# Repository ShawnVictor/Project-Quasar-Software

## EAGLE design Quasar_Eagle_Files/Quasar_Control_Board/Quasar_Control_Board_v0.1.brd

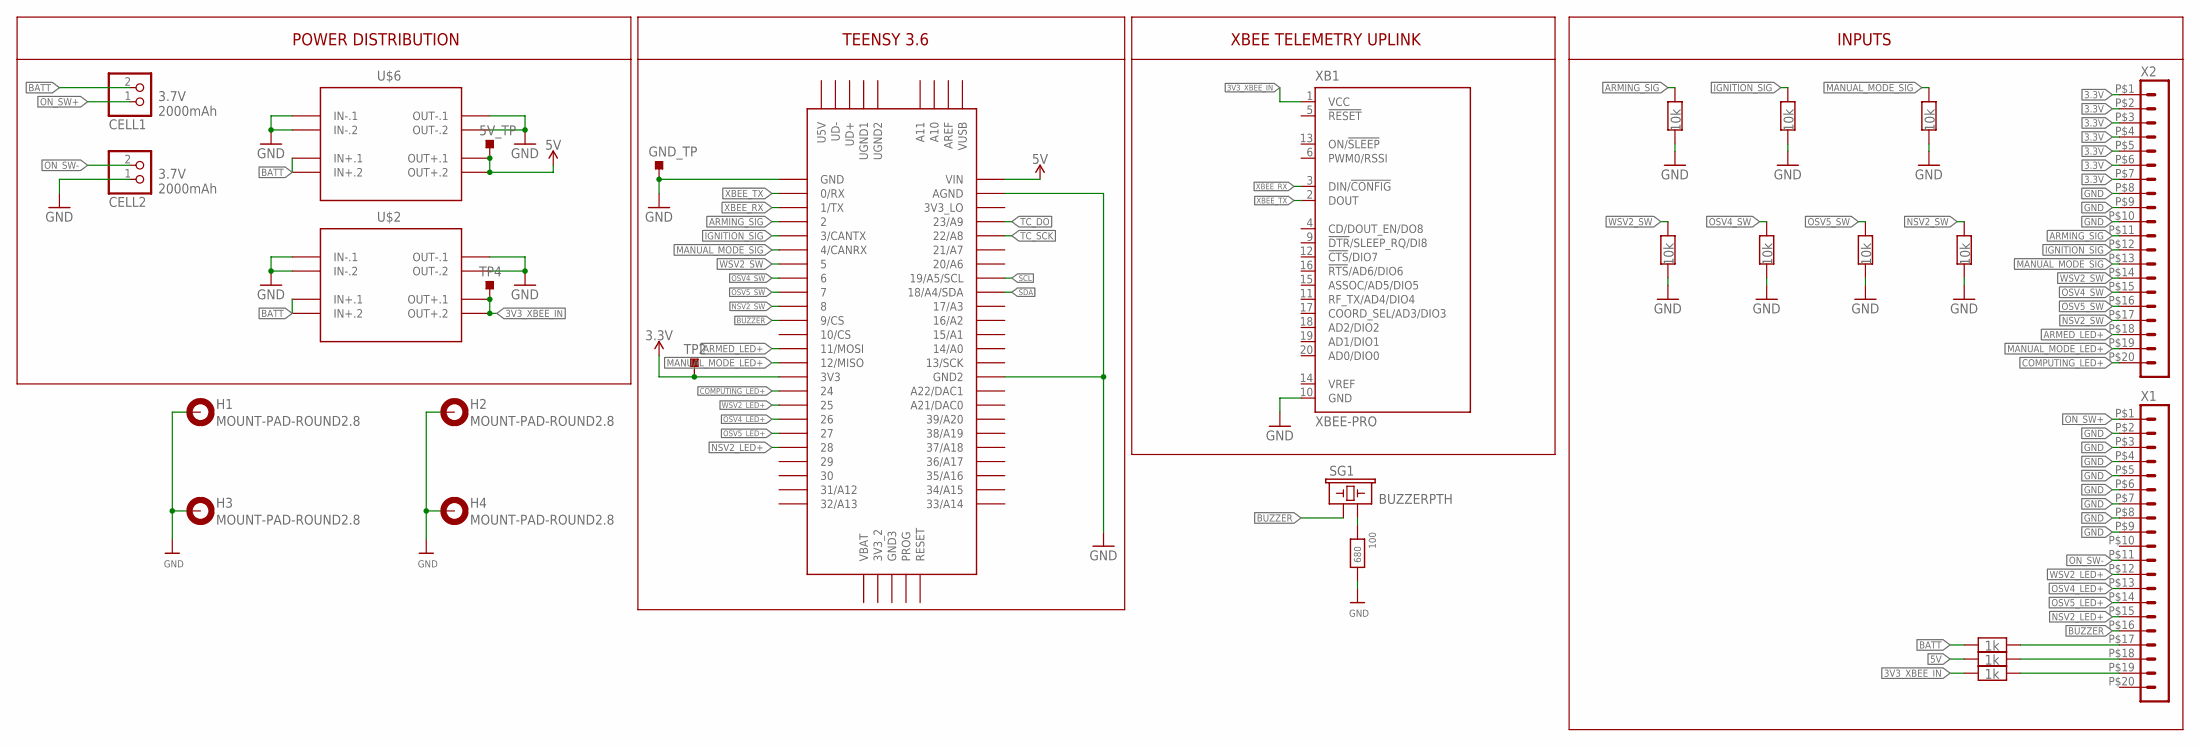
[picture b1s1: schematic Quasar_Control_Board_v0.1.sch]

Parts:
5V_TP: TESTPOINT_TPS-SMD-10SN; TESTPOINT_SMD-10SN
100: 680; 0603
CELL1, CELL2: JSTPH; JSTPH2
GND_TP: TESTPOINT_TPS-SMD-10SN; TESTPOINT_SMD-10SN
H1, H2, H3, H4: MOUNT-PAD-ROUND2.8; 2,8-PAD
R1, R2, R3, R4, R5, R6, R7: 10k; 0805
R8, R9, R10: 1k; 0805
SG1: BUZZERPTH; BUZZER-12MM
TP2, TP4: TESTPOINT_TPS-SMD-10SN; TESTPOINT_SMD-10SN
U$1: TEENSY_3.5/3.6
U$2, U$6: 12V_LC_REG; DC-DC-STEP-DOWN-MP1584
X1, X2: HEADER_POS20_44914-2001; 44914-2001
XB1: XBEE-PRO

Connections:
3.3V: TP2.TP, U$1.3V3, X2.P$1 (1), X2.P$2 (2), X2.P$3 (3), X2.P$4 (4), X2.P$5 (5), X2.P$6 (6), X2.P$7 (7)
3V3_XBEE_IN: R10.2, TP4.TP, U$2.OUT+.1, U$2.OUT+.2, XB1.1 (VCC)
5V: 5V_TP.TP, R9.2, U$1.VIN, U$6.OUT+.1, U$6.OUT+.2
ARMED_LED+: U$1.11/MOSI, X2.P$18 (18)
ARMING_SIG: R1.1, U$1.2, X2.P$11 (11)
BATT: CELL1.2, R8.2, U$2.IN+.1, U$2.IN+.2, U$6.IN+.1, U$6.IN+.2
BUZZER: SG1.+ (1), U$1.9/CS, X1.P$16 (16)
COMPUTING_LED+: U$1.24, X2.P$20 (20)
GND: 100.2, CELL2.1, GND_TP.TP, H1.B2,8, H2.B2,8, H3.B2,8, H4.B2,8, R1.2, R2.2, R3.2, R4.2, R5.2, R6.2, R7.2, U$1.AGND, U$1.GND, U$1.GND2, U$2.IN-.1, U$2.IN-.2, U$2.OUT-.1, U$2.OUT-.2, U$6.IN-.1, U$6.IN-.2, U$6.OUT-.1, U$6.OUT-.2, X1.P$2 (2), X1.P$3 (3), X1.P$4 (4), X1.P$5 (5), X1.P$6 (6), X1.P$7 (7), X1.P$8 (8), X1.P$9 (9), X2.P$8 (8), X2.P$9 (9), X2.P$10 (10), XB1.10 (GND)
IGNITION_SIG: R2.1, U$1.3/CANTX, X2.P$12 (12)
MANUAL_MODE_LED+: U$1.12/MISO, X2.P$19 (19)
MANUAL_MODE_SIG: R3.1, U$1.4/CANRX, X2.P$13 (13)
unnamed: R8.1, X1.P$17 (17)
unnamed: R9.1, X1.P$18 (18)
unnamed: R10.1, X1.P$19 (19)
unnamed: 100.1, SG1.- (2)
NSV2_LED+: U$1.28, X1.P$15 (15)
NSV2_SW: R7.1, U$1.8, X2.P$17 (17)
ON_SW+: CELL1.1, X1.P$1 (1)
ON_SW-: CELL2.2, X1.P$11 (11)
OSV4_LED+: U$1.26, X1.P$13 (13)
OSV4_SW: R5.1, U$1.6, X2.P$15 (15)
OSV5_LED+: U$1.27, X1.P$14 (14)
OSV5_SW: R6.1, U$1.7, X2.P$16 (16)
SCL: U$1.19/A5/SCL
SDA: U$1.18/A4/SDA
TC_DO: U$1.23/A9
TC_SCK: U$1.22/A8
WSV2_LED+: U$1.25, X1.P$12 (12)
WSV2_SW: R4.1, U$1.5, X2.P$14 (14)
XBEE_RX: U$1.1/TX, XB1.3 (DIN/!CONFIG)
XBEE_TX: U$1.0/RX, XB1.2 (DOUT)

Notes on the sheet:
TEENSY 3.6
XBEE TELEMETRY UPLINK
POWER DISTRIBUTION
3.7V 2000mAh
INPUTS

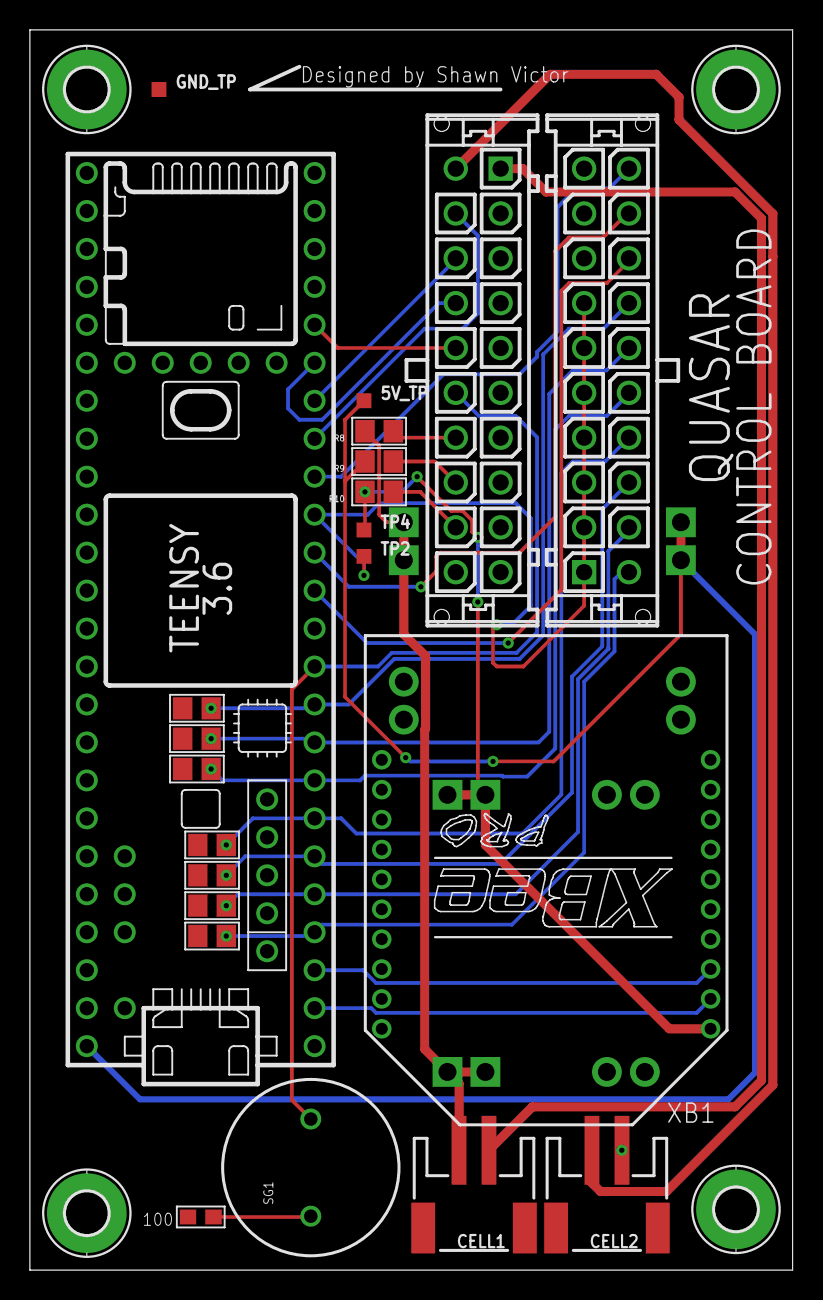
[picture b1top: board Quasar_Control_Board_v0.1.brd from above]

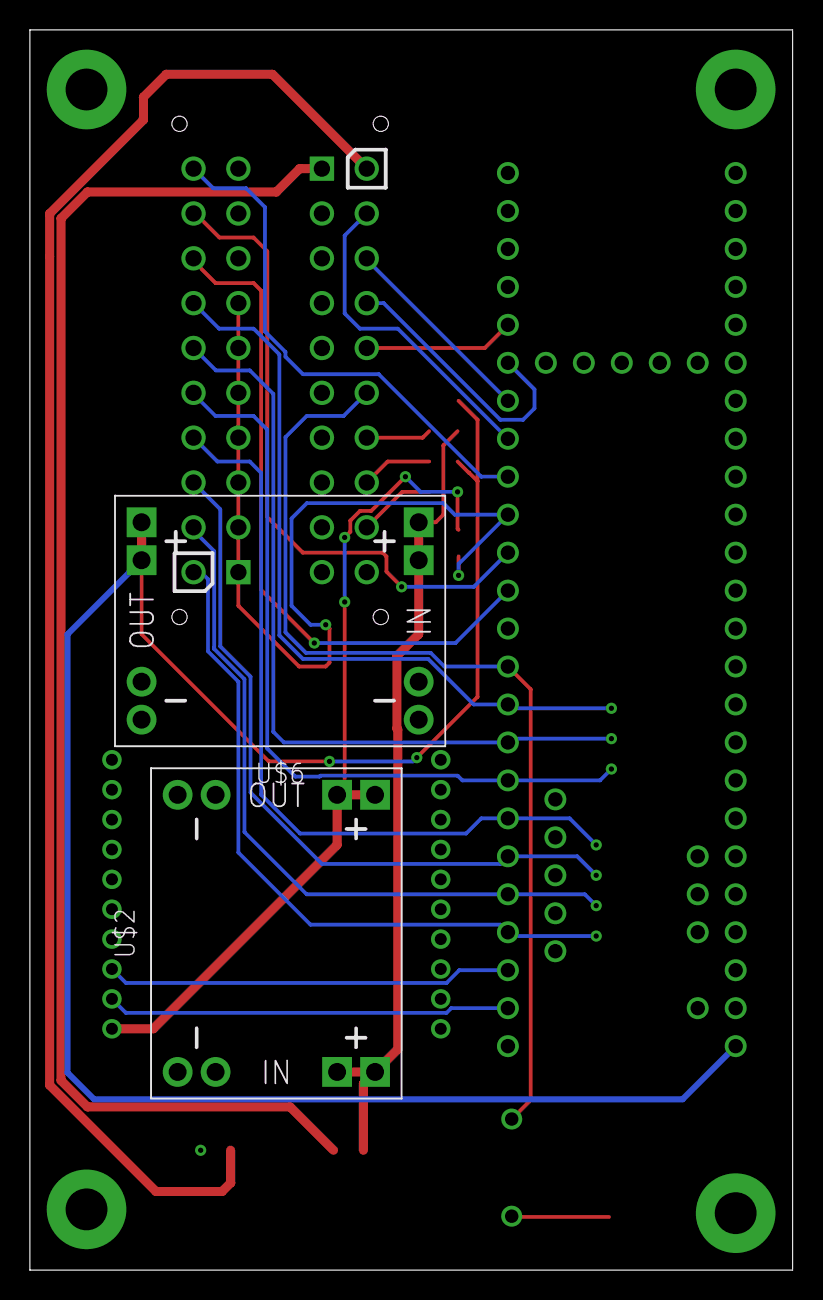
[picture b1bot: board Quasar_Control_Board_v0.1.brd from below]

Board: 2 copper layers, 51.0 x 83.0 mm, 28 parts (2 on the bottom side), 28 nets.

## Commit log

2020-02-04 Added in Globals and Pin Comments.
2020-02-05 Added in macros for each pin
2020-02-08 added all getter functions and serial printing functionality. Some issues, need to test further
2020-02-09 Added code for receiveing data
2020-02-09 Fixed igniter RX code.
2020-02-26 Fixed Thread Break Issue & TC work now.
2020-03-15 Cleaned up Folders & Added Processing Script.
2020-03-15 Copy & Pasted from prototype files.
2020-03-15 Cleaned up code & Added Pin Declarations at top.
2020-03-15 Added in Eagle Files.
2020-03-15 Fixed Timing Issue. Code is a bit more stable.
2020-03-15 Fixed the Heartbeat. Output a bit more stable.
2020-03-16 Cleaned up Macros, Cleaned up PinModes.
2020-03-16 Added Input and Output Update Functions.
2020-03-24 Added more annotations for Functions.
2020-03-24 More added functions.
2020-04-17 Integrated DAQ Code. Working on Control Board Code.

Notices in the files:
parts and their libraries:
diy-modules: Released under the Creative Commons Attribution 4.0 International License: http://creativecommons.org/licenses/by/4.0
SparkFun-PowerSymbols: Licensing: Creative Commons ShareAlike 4.0 International - https://creativecommons.org/licenses/by-sa/4.0
